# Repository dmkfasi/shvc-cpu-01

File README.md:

# SHVC-CPU-01

This is a set of electronic schematics to preserve and recreate Super Family Computer also known as Super NES. Based on PDF files created by *Jonathon W. Donaldson* and *arzi84*.

Designed using [KiCAD EDA](https://kicad.org/).

### The primary goal of this project is to verify publicly available schematics for SNS-CPU-GPM-01 (and other revisions) by implementing these in hardware;

The secondary goals of this project are as follows:
1. Recreate the PCB using mixture of original and modern components to fit smaller size case, possibly for portable variant;
1. Get rid of unused components (such as RF modulator, extension ports, etc) or replace them with custom sub-boards or CPLD/FPGA components;
1. Fiddle around with analogue RGB output from S-PPU2 and sniff data bus for possible digital to digital (or digital to VGA) video output;
1. Design a breakout board for video subsystem (S-PPU1, S-PPU2, SRAM) for purpose of BSNES authors to connect such board to a PC and figure out more details for more accurate emulation:
 (drawings by Rodrigo Copetti)

Present limitations:
* ~~S-WRAM chip package is unknown, seems like a custom one, need to measure actual chip and footprint~~ ~~Done, but with impresice tool~~ Verified with digital calipers;
* ~~F411 CIC chip footprint needs verification~~ ~~Done, verified but with imprecise tool~~ Confirmed, see notes below;
* ~~S-SMP QFP-64 14x20mm needs custom designed footprint~~ ~~Done, needs verification against real chip~~ Confirmed QFP-64 14x20mm;
* My reference board is SNS-CPU-RGB-01;

---
Notes and references:

* S-CPU, S-PPU1, S-PPU2 and S-DSP seem to be PQFP-100 14x20mm
* SRAM, PSRAM are standard SOP-28, footprint redesigned
* F411 CIC seems to be SSOP-18 6.0x7.6mm, custom footprint designed
* S-SMP assigned PQFP-64 1.0mm pitch footprint
* S-WRAM assigned SOP-64 0.8mm pitch footprint, 26.6x11.0mm body

* Pin pitch = 2.5mm (not 2.54mm)
* PCB thickness = 1.2mm
* SNS-CPU-RGB-01 PCB thickness = 1.6mm

 (drawings by Rodrigo Copetti)

---

# Work in progress

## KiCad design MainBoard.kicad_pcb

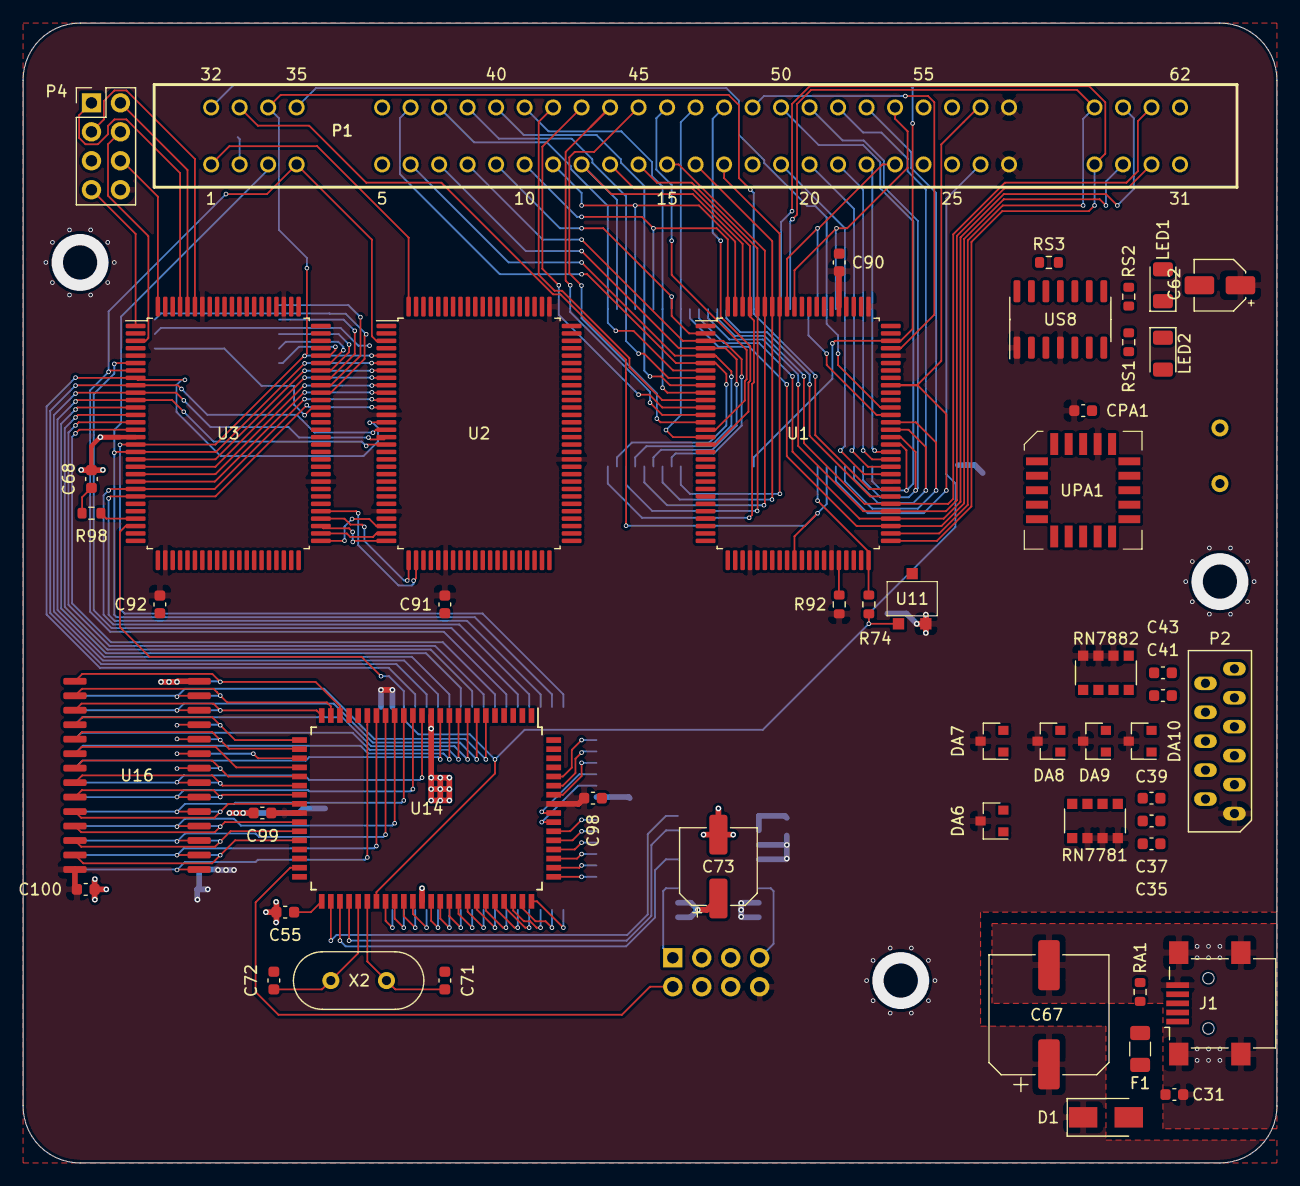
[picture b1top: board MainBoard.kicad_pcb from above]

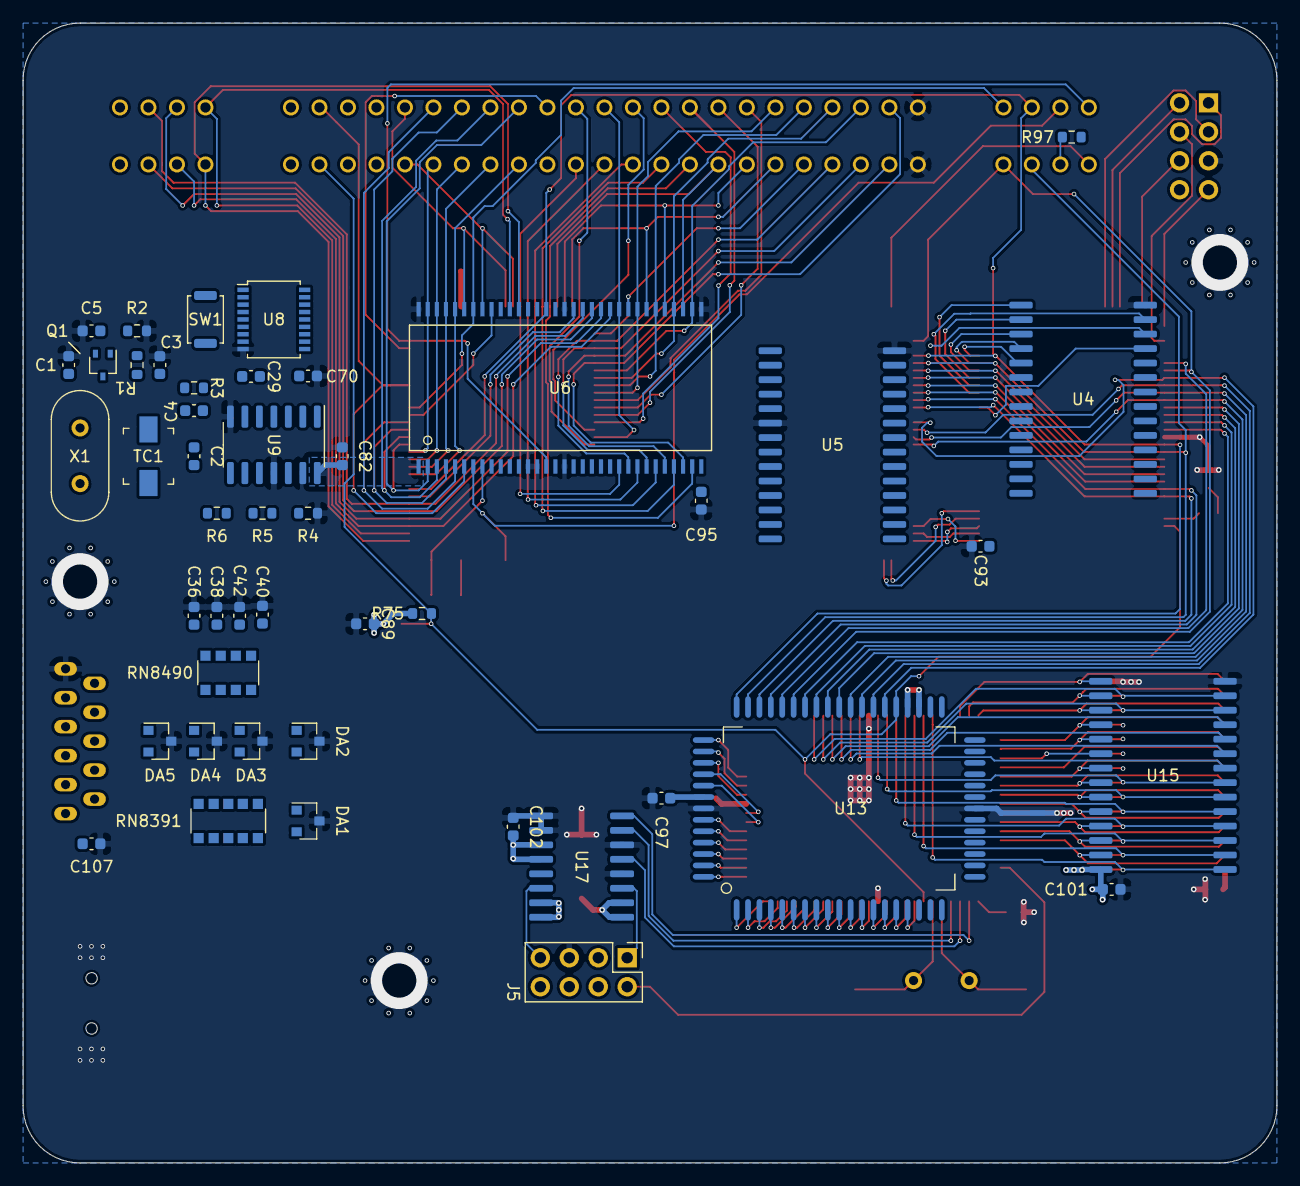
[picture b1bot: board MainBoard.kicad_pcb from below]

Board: 4 copper layers, 110.0 x 100.0 mm, 98 parts (47 on the bottom side), 236 nets.

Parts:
C1: 47pF; C_0603_1608Metric
C2: 15pF; C_0603_1608Metric
C3: 10pF; C_0603_1608Metric
C4: 100pF; C_0603_1608Metric
C5, C107: 0.01uF; C_0603_1608Metric
C29, C82, C90, C91, C92, C93, C95, C97, C98, C99, C100, C101, C102: 0.1uF; C_0603_1608Metric
C31: 0.01uF 50V; C_0603_1608Metric
C35, C36, C37, C38, C39, C40, C41, C42, C43: 330pF; C_0603_1608Metric
C55: (0); C_0603_1608Metric
C62: 2.2uF; CP_Elec_4x5.4
C67: 1000uF 25V; CP_Elec_10x12.6
C68: 56pF; C_0603_1608Metric
C70: 82pF; C_0603_1608Metric
C71, C72: 3pF; C_0603_1608Metric
C73: 47uF (10V); CP_Elec_6.3x5.4
C89: 100nF; C_0603_1608Metric
CPA1: 100nF; C_0603_1608Metric
D1: PB1100; D_SMA
DA1, DA2, DA3, DA4, DA5: BAT54A; SOT-23
DA6, DA7, DA8, DA9, DA10: BAT54C; SOT-23
F1: Polyfuse; Fuse_1206_3216Metric
J1: USB B Mini; USB_Mini-B_Lumberg_2486_01_Horizontal
J5: Audio Out Port; PinHeader_2x04_P2.54mm_Vertical
LED1: GREEN; LED_1206_3216Metric
LED2: RED; LED_1206_3216Metric
P1: CARTRIDGE_SLOT; SNES_RETRODE_SLOT
P2: FRONT_PANEL_CONNECTOR; SNES_JOYPAD_PORT_ZIP-11
P4: Multi AV Out; PinHeader_2x04_P2.54mm_Vertical
Q1: 2SC4699; SOT-323_SC-70
R1: 56K; R_0603_1608Metric
R2, R4: 210; R_0603_1608Metric
R3: 1.2K; R_0603_1608Metric
R5: 39; R_0603_1608Metric
R6, R75: 100K; R_0603_1608Metric
R74: 1K; R_0603_1608Metric
R92, R97: 10K; R_0603_1608Metric
R98: 100; R_0603_1608Metric
RA1: 100; R_0603_1608Metric
RN7781, RN7882: 10K; R_Array_Convex_4x1206
RN8391: 100; R_Array_Convex_5x1206
RN8490: 100; R_Array_Convex_4x1206
RS1, RS2: 180; R_0603_1608Metric
RS3: 10K; R_0603_1608Metric
SW1: RESET; SW_Push_SPST_NO_Alps_SKRK
TC1: 20pF; C_Trimmer_Murata_TZB4-A
U1: S-CPU; PQFP-100_14x20mm_P0.65mm
U2: S-PPU1; PQFP-100_14x20mm_P0.65mm
U3: S-PPU2; PQFP-100_14x20mm_P0.65mm
U4, U5: SRAM; SOP-28-330mil_P1.27mm
U6: S-WRAM; SOP-64_10.9x26.5mm_P0.8mm
U8: CIC; SSOP-18_4.4x6.5mm_P0.65mm
U9: HCU04; SOIC-14_3.9x8.7mm_P1.27mm
U11: PST529D; MMP-3A
U13: S-SMP; PQFP-64_14x20mm_P1.0mm
U14: S-DSP; PQFP-80_14x20mm_P0.8mm
U15, U16: PSRAM; SOP-28-330mil_P1.27mm
U17: UPD6376; SOP-16-300mil_P1.27mm
UPA1: 16V8; PLCC-20
US8: SuperCIC; SOIC-14_3.9x8.7mm_P1.27mm
X1: 21.47727 MHz; Crystal_HC49-4H_Vertical
X2: 24.576MHz; Crystal_HC49-4H_Vertical

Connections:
/3.58M: P4.4, U3.3
/4016.D0: DA3.2, DA8.1, RN7781.3, RN8391.8, U1.32
/4016.D1: DA3.1, DA8.2, RN7882.1, RN8490.7, U1.33
/4017.D0: DA4.2, DA9.1, RN7781.2, RN8391.9, U1.27
/4017.D1: DA4.1, DA9.2, RN7882.2, RN8490.6, U1.28
/$214F_PATCH: UPA1.13, US8.3
/AUDIO_LOUT: J5.1, U17.11
/AUDIO_ROUT: J5.7, U17.6
/CA0: P1.17, U1.93, U6.23
/CA1: P1.16, U1.94, U6.25
/CA2: P1.15, U1.95, U6.27
/CA3: P1.14, U1.96, U6.29
/CA4: P1.13, U1.97, U6.31
/CA5: P1.12, U1.98, U6.35
/CA6: P1.11, U1.99, U6.37
/CA7: P1.10, U1.100, U6.39
/CA8: P1.9, U1.2, U6.41
/CA9: P1.8, U1.3, U6.24
/CA10: P1.7, U1.4, U6.26
/CA11: P1.6, U1.5, U6.28
/CA12: P1.37, U1.6, U6.30
/CA13: P1.38, U1.7, U6.34
/CA14: P1.39, U1.8, U6.36
/CA15: P1.40, U1.9, U6.38
/CA16: P1.41, U1.10, U6.40
/CA17: P1.42, U1.11
/CA18: P1.43, U1.12
/CA19: P1.44, U1.13
/CA20: P1.45, U1.14
/CA21: P1.46, U1.15
/CA22: P1.47, U1.16, U6.42
/CA23: P1.48, U1.17
/CART_SOUND-L: J5.3, P1.31
/CART_SOUND-R: J5.6, P1.62
/CHR0: U2.85, U3.46
/CHR1: U2.84, U3.47
/CHR2: U2.83, U3.48
/CHR3: U2.82, U3.49
/CIC0: P1.24, U8.2, US8.9
/CIC1: P1.55, U8.1, US8.10
/CIC2: P1.25, U8.11, US8.8
/CIC3: C70.1, P1.56, U9.2
/CIC_CL1: U8.7, U9.4, US8.2
/CIC_RESET: C29.2, RS3.2, SW1.1, U8.8, US8.13
/COLOR0: U2.90, U3.41
/COLOR1: U2.89, U3.42
/COLOR2: U2.88, U3.43
/D0: P1.19, U1.60, U2.21, U3.15, U6.60, U13.45
/D1: P1.20, U1.61, U2.20, U3.14, U6.61, U13.44
/D2: P1.21, U1.62, U2.19, U3.13, U6.62, U13.43
/D3: P1.22, U1.63, U2.18, U3.12, U6.63, U13.42
/D4: P1.50, U1.64, U2.17, U3.11, U6.2, U13.41, UPA1.16, UPA1.17, UPA1.18, UPA1.19
/D5: P1.51, U1.65, U2.16, U3.10, U6.3, U13.40
/D6: P1.52, U1.66, U2.15, U3.9, U6.4, U13.39
/D7: P1.53, U1.67, U2.14, U3.8, U6.5, U13.38
/FIELD: U2.95, U3.36
/HBLANK: U1.43, U3.25
/JPCLK1: DA2.2, DA7.1, RN8391.7, U1.35
/JPCLK2: DA2.1, DA7.2, RN8490.8, U1.36
/JPIO6: DA5.2, DA10.1, RN7781.1, RN8391.10, U1.25
/JPIO7: DA5.1, DA10.2, RN7882.3, RN8490.5, U1.26, U3.29
/JPSTR: DA1.1, DA6.2, RN8391.6, U1.37
/MA0: U14.9, U15.10, U16.10
/MA1: U14.10, U15.9, U16.9
/MA2: U14.11, U15.8, U16.8
/MA3: U14.13, U15.7, U16.7
/MA4: U14.14, U15.6, U16.6
/MA5: U14.15, U15.5, U16.5
/MA6: U14.16, U15.4, U16.4
/MA7: U14.17, U15.3, U16.3
/MA8: U14.34, U15.25, U16.25
/MA9: U14.32, U15.24, U16.24
/MA10: U14.29, U15.21, U16.21
/MA11: U14.31, U15.23, U16.23
/MA12: U14.18, U15.2, U16.2
/MA13: U14.35, U15.26, U16.26
/MA14: U14.19, U15.1, U16.1
/MD0: U14.8, U15.11, U16.11
/MD1: U14.7, U15.12, U16.12
/MD2: U14.6, U15.13, U16.13
/MD3: U14.22, U15.15, U16.15
/MD4: U14.23, U15.16, U16.16
/MD5: U14.24, U15.17, U16.17
/MD6: U14.25, U15.18, U16.18
/MD7: U14.26, U15.19, U16.19
/PA0: P1.28, U1.51, U2.12, U3.24, U6.53, U13.49, UPA1.1
/PA1: P1.59, U1.52, U2.11, U3.23, U6.54, U13.48, UPA1.5
/PA2: P1.29, U1.53, U2.10, U3.22, U6.43, UPA1.2
/PA3: P1.60, U1.54, U2.9, U3.21, U6.44, UPA1.6
/PA4: P1.30, U1.55, U2.8, U3.20, U6.45, UPA1.3
/PA5: P1.61, U1.56, U2.7, U3.19, U6.46, UPA1.7
/PA6: P1.3, U1.57, U2.6, U3.18, U6.47, U13.50, UPA1.4
/PA7: P1.34, U1.58, U2.5, U3.17, U6.50, U13.51, UPA1.8
/PRIO0: U2.87, U3.44
/PRIO1: U2.86, U3.45
/Post_Amplifier: DA1.2, DA6.1
/REFRESH: P1.33, U1.40, U6.7
/SCLK: C55.1, U9.1, U9.3, U14.41
/SYSCK: P1.57, U1.72, U6.6
/VA14: U2.47, U4.1, U5.1
/VAA0: U2.76, U5.10
/VAA1: U2.75, U5.9
/VAA2: U2.74, U5.8
/VAA3: U2.73, U5.7
/VAA4: U2.72, U5.6
/VAA5: U2.71, U5.5
/VAA6: U2.70, U5.4
/VAA7: U2.69, U5.3
/VAA8: U2.68, U5.25
/VAA9: U2.67, U5.24
/VAA10: U2.66, U5.21
/VAA11: U2.65, U5.23
/VAA12: U2.64, U5.2
/VAA13: U2.63, U5.26
/VAB0: U2.61, U4.10
/VAB1: U2.60, U4.9
/VAB2: U2.59, U4.8
/VAB3: U2.58, U4.7
/VAB4: U2.57, U4.6
/VAB5: U2.56, U4.5
/VAB6: U2.55, U4.4
/VAB7: U2.54, U4.3
/VAB8: U2.53, U4.25
/VAB9: U2.52, U4.24
/VAB10: U2.51, U4.21
/VAB11: U2.50, U4.23
/VAB12: U2.49, U4.2
/VAB13: U2.48, U4.26
/VBLANK: U1.44, U3.26
/VDA0: U2.37, U3.60, U5.11
/VDA1: U2.38, U3.61, U5.12
/VDA2: U2.39, U3.62, U5.13
/VDA3: U2.40, U3.63, U5.15
/VDA4: U2.41, U3.64, U5.16
/VDA5: U2.42, U3.65, U5.17
/VDA6: U2.43, U3.66, U5.18
/VDA7: U2.44, U3.67, U5.19
/VDB0: U2.28, U3.51, U3.69, U4.11
/VDB1: U2.29, U3.52, U3.70, U4.12
/VDB2: U2.30, U3.53, U3.71, U4.13
/VDB3: U2.31, U3.54, U3.72, U4.15
/VDB4: U2.32, U3.55, U3.73, U4.16
/VDB5: U2.33, U3.56, U3.74, U4.17
/VDB6: U2.34, U3.57, U3.75, U4.18
/VDB7: U2.35, U3.58, U3.76, U4.19
/VIDEO_B: P4.3, U3.95
/VIDEO_G: P4.2, U3.96
/VIDEO_R: P4.1, U3.97
/XIN: P1.1, R4.2, R5.1, U1.48, U2.100, U3.31
/~5MIN: U2.93, U2.94, U2.97, U3.37, U3.38, U3.50
/~CE0: U14.28, U16.20
/~CE1: U14.27, U15.20
/~CPURD: P1.23, U1.92, U6.57
/~CPUWR: P1.54, U1.91, U6.59
/~HCLD: U2.92, U3.39
/~IRQ: P1.18, R92.2, U1.46
/~MUTE: J5.2, U14.39
/~OE: U14.30, U15.22, U16.22
/~PARD: P1.4, U1.68, U2.3, U3.7, U6.56, U13.46, UPA1.9
/~PAWR: P1.35, U1.69, U2.4, U3.6, U6.58, U13.47
/~RAMSEL: P1.32, U1.78, U6.15
/~RESET: U3.34, U8.10, US8.11
/~RESOUT0: U2.98, U3.33
/~RESOUT1: P1.26, R74.1, R74.2, R75.1, U1.50, U3.28, U6.8, U11.2, U13.37, U14.47
/~ROMSEL: P1.49, U1.77
/~VAWR: U2.78, U5.27
/~VBWR: U2.79, U4.27
/~VCLD: U2.91, U3.40
/~VIDEO_BURST: P4.6, U3.100
/~VIDEO_CSYNC: P4.7, U3.1
/~VRD: U2.80, U4.22, U5.22
/~WE: U14.36, U15.27, U16.27
GND: C1.2, C3.2, C5.2, C31.1, C35.2, C36.2, C37.2, C38.2, C39.2, C40.1, C41.2, C42.2, C43.2, C55.2, C67.2, C68.2, C70.2, C71.1, C72.1, C73.2, C82.2, C89.2, C90.1, C91.1, C92.1, C93.1, C95.1, C97.2, C98.1, C99.2, C100.1, C101.1, C102.1, C107.2, CPA1.2, DA1.3, DA2.3, DA3.3, DA4.3, DA5.3, J1.5, J1.6, J5.5, LED1.1, LED2.1, P1.5, P1.36, P2.11, P4.5, R2.1, R4.1, RS3.1, U1.18, U1.29, U1.30, U1.31, U1.41, U1.42, U1.47, U1.49, U1.73, U1.74, U1.75, U1.79, U1.90, U2.1, U2.2, U2.22, U2.23, U2.24, U2.25, U2.27, U2.45, U2.77, U2.96, U2.99, U3.16, U3.30, U3.35, U3.68, U3.90, U3.91, U3.92, U3.93, U3.98, U3.99, U4.14, U4.20, U5.14, U5.20, U6.13, U6.14, U6.17, U6.33, U6.48, U6.64, U8.9, U9.7, U9.11, U9.13, U11.3, U13.26, U13.58, U14.12, U14.37, U14.38, U14.52, U15.14, U16.14, U17.1, U17.2, U17.12, U17.14, UPA1.10, US8.7, US8.12, US8.14
unnamed: C1.1, X1.2
unnamed: C2.1, TC1.1, X1.1
unnamed: C2.2, C3.1, C4.2, Q1.3, R1.2, R3.1, TC1.2
unnamed: C4.1, R6.2, U9.9
unnamed: C5.1, Q1.2, R2.2
unnamed: C31.2, D1.2, F1.2
unnamed: C35.1, P2.2, RN8391.1
unnamed: C36.1, P2.3, RN8490.4
unnamed: C37.1, P2.4, RN8391.2
unnamed: C38.1, P2.5, RN8490.3
unnamed: C39.1, P2.6, RN8391.3
unnamed: C40.2, P2.7, RN8490.2
unnamed: C41.1, P2.8, RN8391.4
unnamed: C42.1, P2.9, RN8490.1
unnamed: C43.1, P2.10, RN8391.5
unnamed: C62.2, U8.3
unnamed: C68.1, R98.2
unnamed: C71.2, U14.46, X2.2
unnamed: C72.2, U14.45, X2.1
unnamed: C73.1, U17.9, U17.10
unnamed: F1.1, J1.1
unnamed: J1.2, RA1.1
unnamed: J1.3, RA1.2
unnamed: LED1.2, RS2.1
unnamed: LED2.2, RS1.2
unnamed: P1.2, R97.2
unnamed: Q1.1, R1.1
unnamed: R5.2, U9.6
unnamed: R6.1, U9.5, U9.8
unnamed: R98.1, U3.27
unnamed: RS1.1, US8.6
unnamed: RS2.2, US8.5
unnamed: U13.1, U14.64
unnamed: U13.2, U14.63
unnamed: U13.3, U14.62
unnamed: U13.4, U14.61
unnamed: U13.5, U14.60
unnamed: U13.6, U14.59
unnamed: U13.7, U14.58
unnamed: U13.8, U14.57
unnamed: U13.9, U14.56
unnamed: U13.10, U14.55
unnamed: U13.11, U14.54
unnamed: U13.12, U14.53
unnamed: U13.13, U14.51
unnamed: U13.14, U14.50
unnamed: U13.15, U14.49
unnamed: U13.16, U14.48
unnamed: U13.52, U14.76
unnamed: U13.53, U14.75
unnamed: U13.54, U14.74
unnamed: U13.55, U14.72
unnamed: U13.56, U14.71
unnamed: U13.59, U14.70
unnamed: U13.60, U14.69
unnamed: U13.61, U14.68
unnamed: U13.62, U14.67
unnamed: U13.63, U14.66
unnamed: U13.64, U14.65
unnamed: U14.42, U17.16
unnamed: U14.43, U17.13
unnamed: U14.44, U17.15
VCC: C29.1, C62.1, C67.1, C82.1, C89.1, C90.2, C91.2, C92.2, C93.2, C95.2, C97.1, C98.2, C99.1, C100.2, C101.2, C102.2, C107.1, CPA1.1, D1.1, DA6.3, DA7.3, DA8.3, DA9.3, DA10.3, J5.8, P1.27, P1.58, P2.1, P4.8, R3.2, R75.2, R92.1, R97.1, RN7781.6, RN7781.7, RN7781.8, RN7882.6, RN7882.7, RN7882.8, SW1.2, U1.1, U1.34, U1.45, U1.59, U1.76, U1.81, U1.85, U2.13, U2.26, U2.36, U2.62, U2.81, U3.5, U3.32, U3.59, U3.83, U3.94, U4.28, U5.28, U6.1, U6.10, U6.11, U6.12, U6.16, U6.32, U6.49, U6.51, U6.52, U8.4, U8.18, U9.14, U11.1, U13.35, U13.36, U13.57, U14.33, U14.73, U15.28, U16.28, U17.3, U17.4, U17.7, U17.8, UPA1.20, US8.1, US8.4

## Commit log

2020-12-21 CIC and S-WRAM added
2020-12-21 S-WRAM finished
2020-12-21 Corrected CIC shape
2020-12-21 Basic S-CPU shape added
2020-12-21 Left side S-CPU added
2020-12-21 Right side S-CPU started
2020-12-21 Right side S-CPU completed
2020-12-21 Joypad front panel connector added
2020-12-21 VRAM completed
2020-12-22 S-PPU1 started
2020-12-22 S-PPU1 left side completed
2020-12-22 S-PPU2 started
2020-12-22 Cartridge Slot started
2020-12-22 Cartridge Slot left side completed
2020-12-22 Cartridge Slot completed
2020-12-23 S-SMP started
2020-12-23 S-SMP left side completed
2020-12-23 S-SMP right side completed
2020-12-23 S-SMP fixed
2020-12-23 S-DSP started
2020-12-23 S-DSP left side completed
2020-12-23 S-DSP right side completed
2020-12-24 S-SMP VSS pins fixed
2020-12-24 S-CPU footprint and datasheet link added
2020-12-24 Footprints added
2020-12-24 S-WRAM package cleared for further clarification
2020-12-24 Basic info about the project
2020-12-24 Local component library added
2020-12-24 Reference material
2020-12-24 Components metadata added
2020-12-24 Diagrams added
2020-12-24 Reference picture
2020-12-24 Local footprint cache
2020-12-24 No need for this
2020-12-25 Proper naming
2020-12-25 Renamed from -cache file
2020-12-25 Initial placement
2020-12-25 UPD6376 audio DAC added
2020-12-25 Cart slot gerber layer
2020-12-25 Chips placed
2020-12-25 Library added
2020-12-26 Body fill colour introduced
2020-12-26 Primary components placed and annotated
2020-12-26 Text alignments and annotations
2020-12-26 Removed
2020-12-26 Current annotation file
2020-12-26 UPD6376 corrected and completed
2020-12-26 Fix to match library components
2020-12-26 Cartridge Slot footprint added
2020-12-26 Cart slot footprint assigned
2020-12-26 Local footprint appointed
2020-12-26 Symbols aligned
2020-12-26 Cart slot footprint added
2020-12-26 Local copy
2020-12-26 Replaced with local copy footprints
2020-12-26 Preliminarily S-WRAM footprint
2020-12-26 Moved to appropriate filename
2020-12-27 JPIO port wired
2020-12-27 S-CPU started
2020-12-27 JPIO connector corrected to fit schematics better
2020-12-27 S-PPU1 + VRAM1
2020-12-27 VRAM1 + VRAM2 + S-PPU1
2020-12-27 VRAM rd/wr bus finished
2020-12-28 Cart slot and PPU somewhat wired up
2020-12-28 Fixed pins to Passive for Front Panel
2020-12-28 S-PPU2 wiring started
2020-12-28 U11 PST529D added
2020-12-28 CIC completed, Xtal started
2020-12-28 Joypad port footprint ZIP-11
2020-12-28 Fixed PST529 size
2020-12-28 U11 added
2020-12-28 S-SMP CPU footprint
2020-12-29 For U11 Power Supervisor
2020-12-29 Fixes to 529, S-DSP and S-PPU2
2020-12-29 XIN added, PPU2 mostly done, S-SMP and S-DSP started
2020-12-30 Passive pin fixes for multiple components
2020-12-30 Mostly complete, no ERC errors/warnings
2020-12-30 Block diagram credits and updated notes
2021-01-02 SuperCIC added, D4 patch added
2021-01-02 SuperCIC added
2021-01-02 Capacitor footprints added
2021-01-02 Most footprints added
2021-01-02 Resistor footprints added
2021-01-02 Missing footprints added
2021-01-02 Meta info updated
2021-01-02 Current netlist
2021-01-02 Pin numbers assigned
2021-01-02 U1 pinout leading 0 removed
2021-01-02 Consolidated for local usage
2021-01-02 214f patch implemented with PLD
2021-01-02 Notes errata, 213f PLD version added
2021-01-02 Used in PLD 213f patch
2021-01-02 3D shape added
2021-01-02 Description added
2021-01-02 Missing footprint added, Notes errata
2021-01-02 Local copy for 3D shapes
2021-01-02 Added somewhat 3D shape, need better version
2021-01-02 Transient shape for S-SMP
2021-01-02 Fixed multiple footprints for UP3
2021-01-02 WIP DRAFT
2021-01-02 Replaced with 1206 size
2021-01-02 Moved to proper name packages3d
2021-01-02 Replacement for 1812
2021-01-02 Reassigned footprints and 3D models
2021-01-02 Fixed footprints for Reset Button, X2 and UPA1
2021-01-03 Correct footprint for SRAM
2021-01-03 3D shape for SRAM
2021-01-03 Current settings
2021-01-03 Fixed footprints for SRAM chips
2021-01-03 S-CPU and S-WRAM mostly wired
2021-01-04 Fixed footprint size for C62, rewired RN7882 for better fit on PCB
2021-01-04 Properly laid out XIN and Gamepad portions, the rest is WIP
2021-01-11 Replaced footprint with 2.54mm pitch for easier routing and debugging
2021-01-11 Design Rules change to fit manufacturer capabilities
2021-01-11 Component layout is done
2021-01-12 Current board layout visualization
2021-01-12 Board current 3D view added
2021-01-13 Correct footprint for SRAM/PSRAM
2021-01-13 Footprint reference for SOP-28 330mil
2021-01-13 Fixed wrong SRAM/PSRAM footprints
2021-01-13 Updated according specs and actual hardware
2021-01-13 Not in use anymore
2021-01-13 Fixed U17 footprint
2021-01-13 Footprints reassigned, playing around PSRAM
2021-01-15 Resized, refilled DC in section, compacted
2021-01-17 Front/Back Silk Screen laid out
2021-01-18 Sound section wiring completed
2021-01-18 Updated PWR net track with to 0.5mm
2021-01-18 Swapped LAUDIO and MUTE on J5 for better PCB layout
2021-01-18 Sound section connected to the main CPU now
2021-01-18 Updated notes
2021-01-23 Fixed pads assignment
2021-01-23 WIP, needs rewiring
2021-01-23 Fixed nasty bug with /XIN /RESET interconnection
2021-01-23 Updated and moved to 10.9x26.5mm
2021-01-23 Updated with actual IC measurements, Courtyard outline fixed
